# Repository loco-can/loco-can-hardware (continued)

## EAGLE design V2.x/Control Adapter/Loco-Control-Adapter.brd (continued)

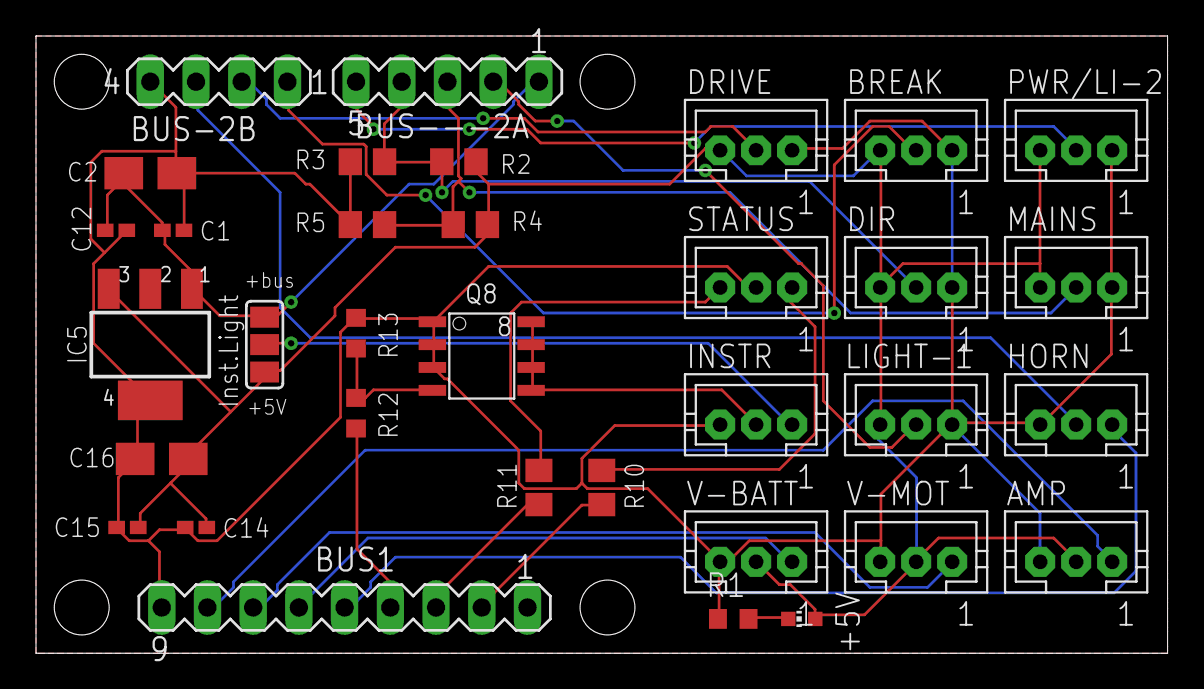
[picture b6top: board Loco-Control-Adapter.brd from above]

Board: 2 copper layers, 62.9 x 34.3 mm, 34 parts (0 on the bottom side), 23 nets.

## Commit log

2023-02-24 initial
2023-02-24 added Loco-CAN icon to motor, servo and switch boards
2023-02-27 new single light and single light akku versions
2023-03-02 design clean up
2023-03-02 create preview images
2023-03-02 diagrams initial state
2023-03-03 documentation sla file created
2023-03-07 Assembly PDF english and german added
2023-03-16 added logos and icons
2023-03-16 update graphics directory
2023-03-21 switch module: can tx status led added manufacturing data for switch module
2023-03-22 add RX/TX led to motor module
2023-03-22 changed sch and brd of motor and switch for RX/TX leds
2023-03-28 added micro module
2023-03-31 updated micro module
2023-04-18 update switch board
2023-08-17 Added Speedometer
2023-08-22 Speedometer added mechanics with housing files added
2023-09-08 XSL-pinout corrected
2026-01-07 minor updates
2026-06-16 Aktualisieren von README.md
